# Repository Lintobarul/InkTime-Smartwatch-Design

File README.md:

# ⌚ InkTime - Open Source Smartwatch

**InkTime** este un smartwatch minimalist și eficient, proiectat pentru a fi open-source. Dispozitivul folosește un ecran E-Paper pentru un consum redus de energie și este motorizat de microcontrolerul nRF52840 (Cortex-M4F) cu suport Bluetooth 5.0.

## 1. Arhitectura Sistemului (Diagrama Bloc)
Dispozitivul este construit în jurul ecosistemului Nordic Semiconductor, integrând următoarele module principale:
* **Unitate Centrală:** nRF52840 (Sistem-on-Chip cu Bluetooth).
* **Afișaj:** E-Paper Display 1.54" (SPI).
* **Senzori:** BMA423 (Accelerometru/Pedometru) via I2C.
* **Management Energie:** BQ25180 (Charger) și MAX17048 (Fuel Gauge).
* **Haptics:** DRV2605 (Haptic Driver) pentru notificări prin vibrații.

---

## 2. Bill of Materials (BOM)

| RefDes | Componentă | Descriere | Link JLC Parts | Datasheet |
| :--- | :--- | :--- | :--- | :--- |
| U1 | nRF52840 | Microcontroller Bluetooth LE | [JLC Part](https://jlcpcb.com/parts/1/nRF52840) | [Datasheet](https://infocenter.nordicsemi.com/pdf/nRF52840_PS_v1.1.pdf) |
| U3 | MAX17048 | Fuel Gauge I2C | [JLC Part](https://jlcpcb.com/parts/1/MAX17048) | [Datasheet](https://datasheets.maximintegrated.com/en/ds/MAX17048-MAX17049.pdf) |
| J1 | 503480-2400 | Conector E-Paper 24-pin | [JLC Part](https://jlcpcb.com/parts/1/503480-2400) | [Datasheet](https://www.molex.com/pdm_docs/sd/5034802400_sd.pdf) |
| IC2 | DRV2605 | Haptic Driver (LRA/ERM) | [JLC Part](https://jlcpcb.com/parts/1/DRV2605) | [Datasheet](https://www.ti.com/lit/ds/symlink/drv2605.pdf) |
| J4 | USB-C 16P | Conector alimentare/date | [JLC Part](https://jlcpcb.com/parts/1/USB-C) | [Datasheet](...) |

---

## 3. Funcționalitate Hardware

### Managementul Energiei și Consum
Dispozitivul este alimentat de o baterie Li-Po de $150 \text{ mAh}$. Încărcarea este gestionată prin portul USB-C, iar nivelul bateriei este raportat prin I2C către procesor.
* **Calcul Autonomie:**
  Presupunând un consum mediu în regim de utilizare normală (Bluetooth activ, refresh ecran la 1 minut) de aproximativ $1.5 \text{ mA}$:
  $$\text{Autonomie} = \frac{150 \text{ mAh}}{1.5 \text{ mA}} = 100 \text{ ore} \approx 4.1 \text{ zile}$$

### Interfețe de Comunicare
* **SPI (Serial Peripheral Interface):** Folosit pentru ecranul E-Paper (semnale SCK, MOSI, CS) pentru a asigura o rată de transfer rapidă a buffer-ului de imagine.
* **I2C (Inter-Integrated Circuit):** Magistrală comună pentru BMA423, MAX17048 și DRV2605, optimizând numărul de pini utilizați.

---

## 4. Alocare Pini (Pinout nRF52840)

Am ales pinii procesorului pe baza funcțiilor speciale și a rutei optime pe PCB:

| Pin | Semnal | Funcție | Motiv |
| :--- | :--- | :--- | :--- |
| **P0.13** | SW_UP | Input | Butonul "SUS", necesită întrerupere pentru trezire. |
| **P0.14** | SW_ENT | Input | Butonul "ENTER", poziționat central. |
| **P1.02** | SW_DN | Input | Butonul "JOS". |
| **P1.13** | EPD_SCK | SPI Clock | Semnal ceas pentru display (Pagina 1.5B). |
| **P1.15** | EPD_MOSI | SPI Data | Date către display. |
| **P0.26** | I2C_SDA | Data | Linie de date pentru magistrala I2C. |
| **P0.27** | I2C_SCL | Clock | Linie de ceas pentru magistrala I2C. |

---

## 5. Design și Layout PCB
* **Grosime Placă:** $1.0 \text{ mm}$ (optimizat pentru carcasă).
* **Layer-ul TOP:** Toate componentele sunt montate pe acest strat pentru a facilita procesul de asamblare automată.
* **Antena RF:** Plasată pe marginea PCB-ului, cu planul de masă (GND) decupat dedesubt pentru a maximiza raza de acțiune Bluetooth.
* **Decuplare:** Condensatoarele de $100 \text{ nF}$ sunt plasate la o distanță de maxim $1 \text{ mm}$ de pinii VDD ai integratelor.

---

## 6. Imaginile Proiectului
### PCB Design (Top View)

### Ansamblu 3D (Exploded View)

---

## 7. Licență
Acest proiect este licențiat sub **GNU General Public License v3.0**. Consultați fișierul `LICENSE` pentru detalii.

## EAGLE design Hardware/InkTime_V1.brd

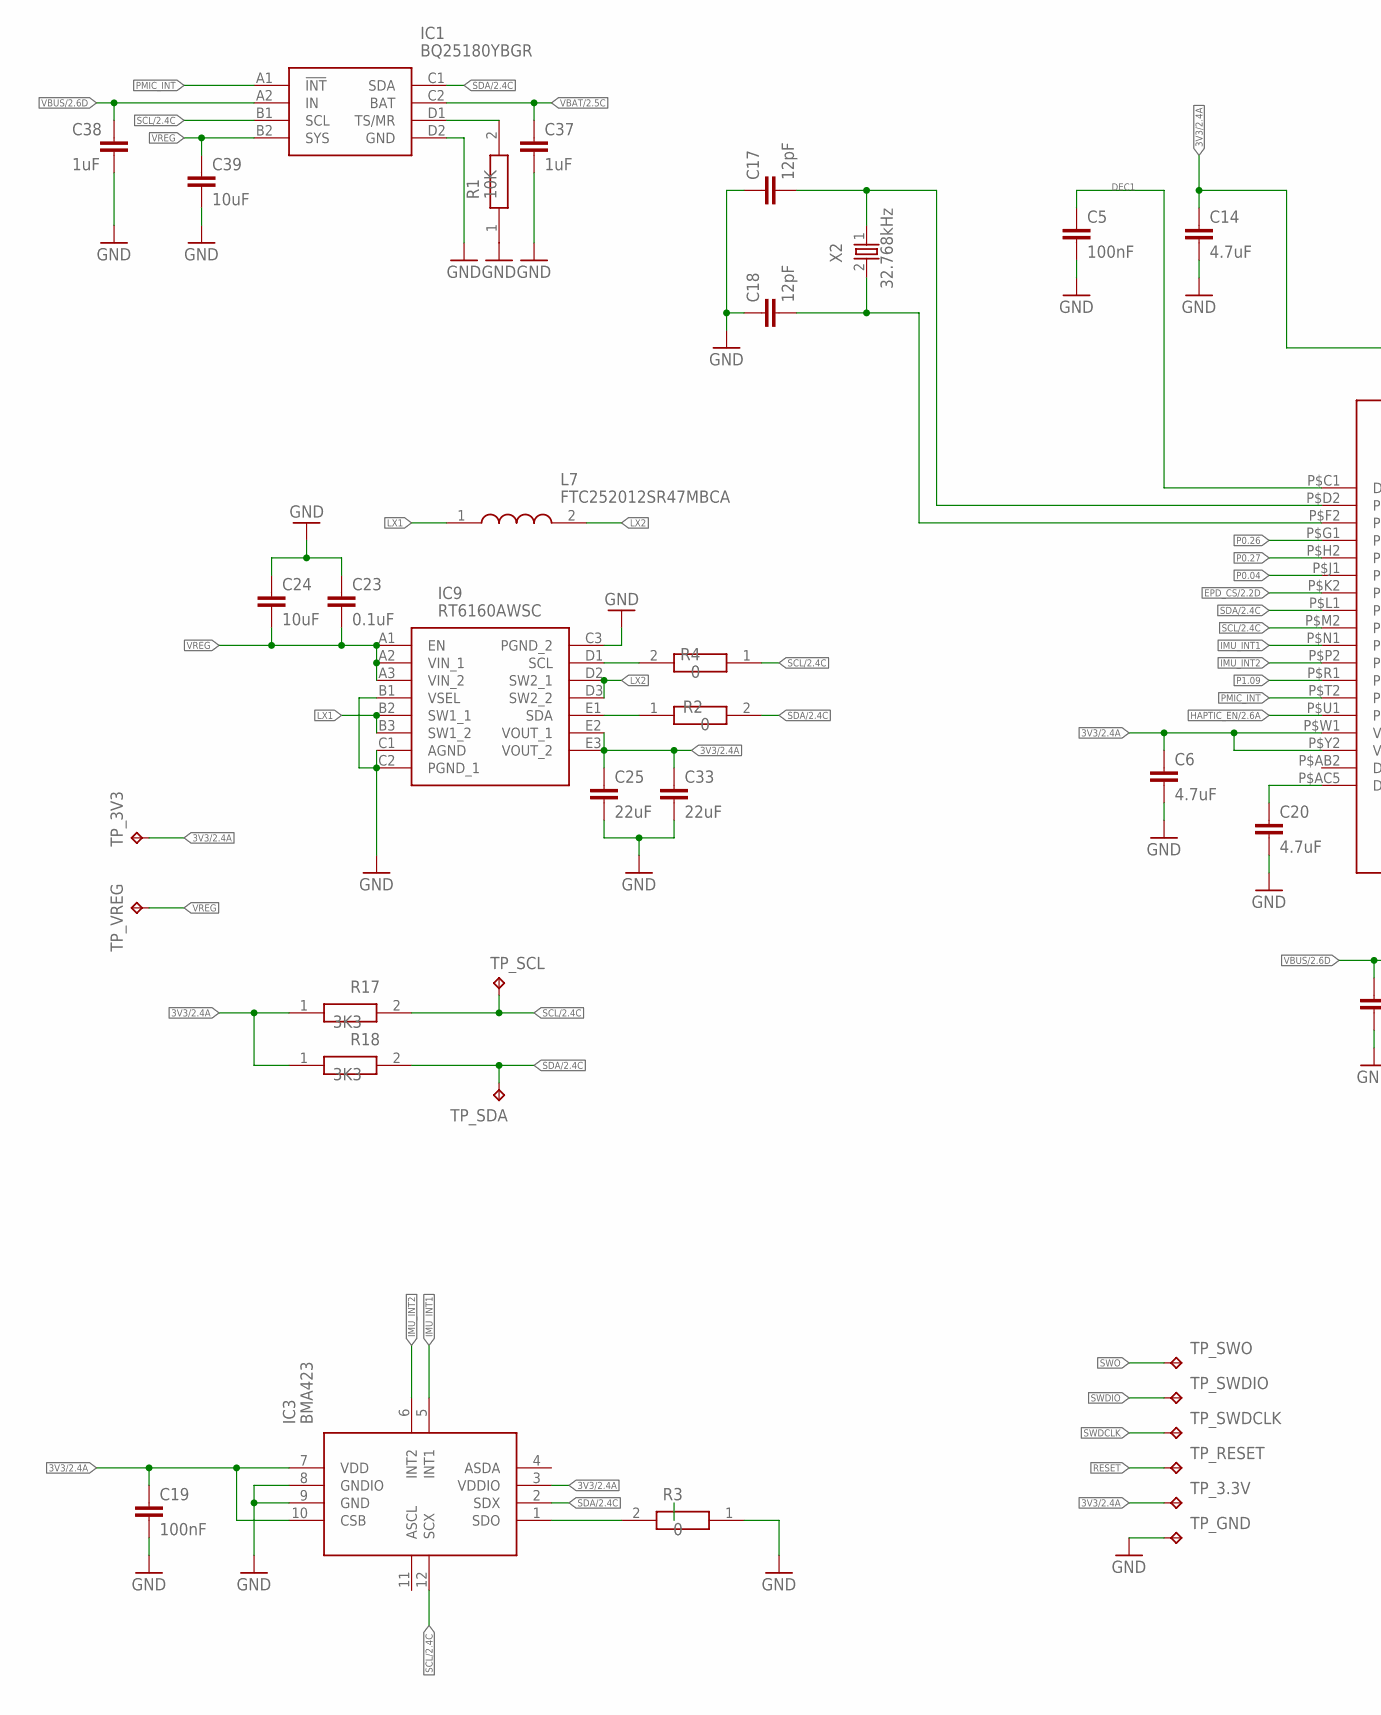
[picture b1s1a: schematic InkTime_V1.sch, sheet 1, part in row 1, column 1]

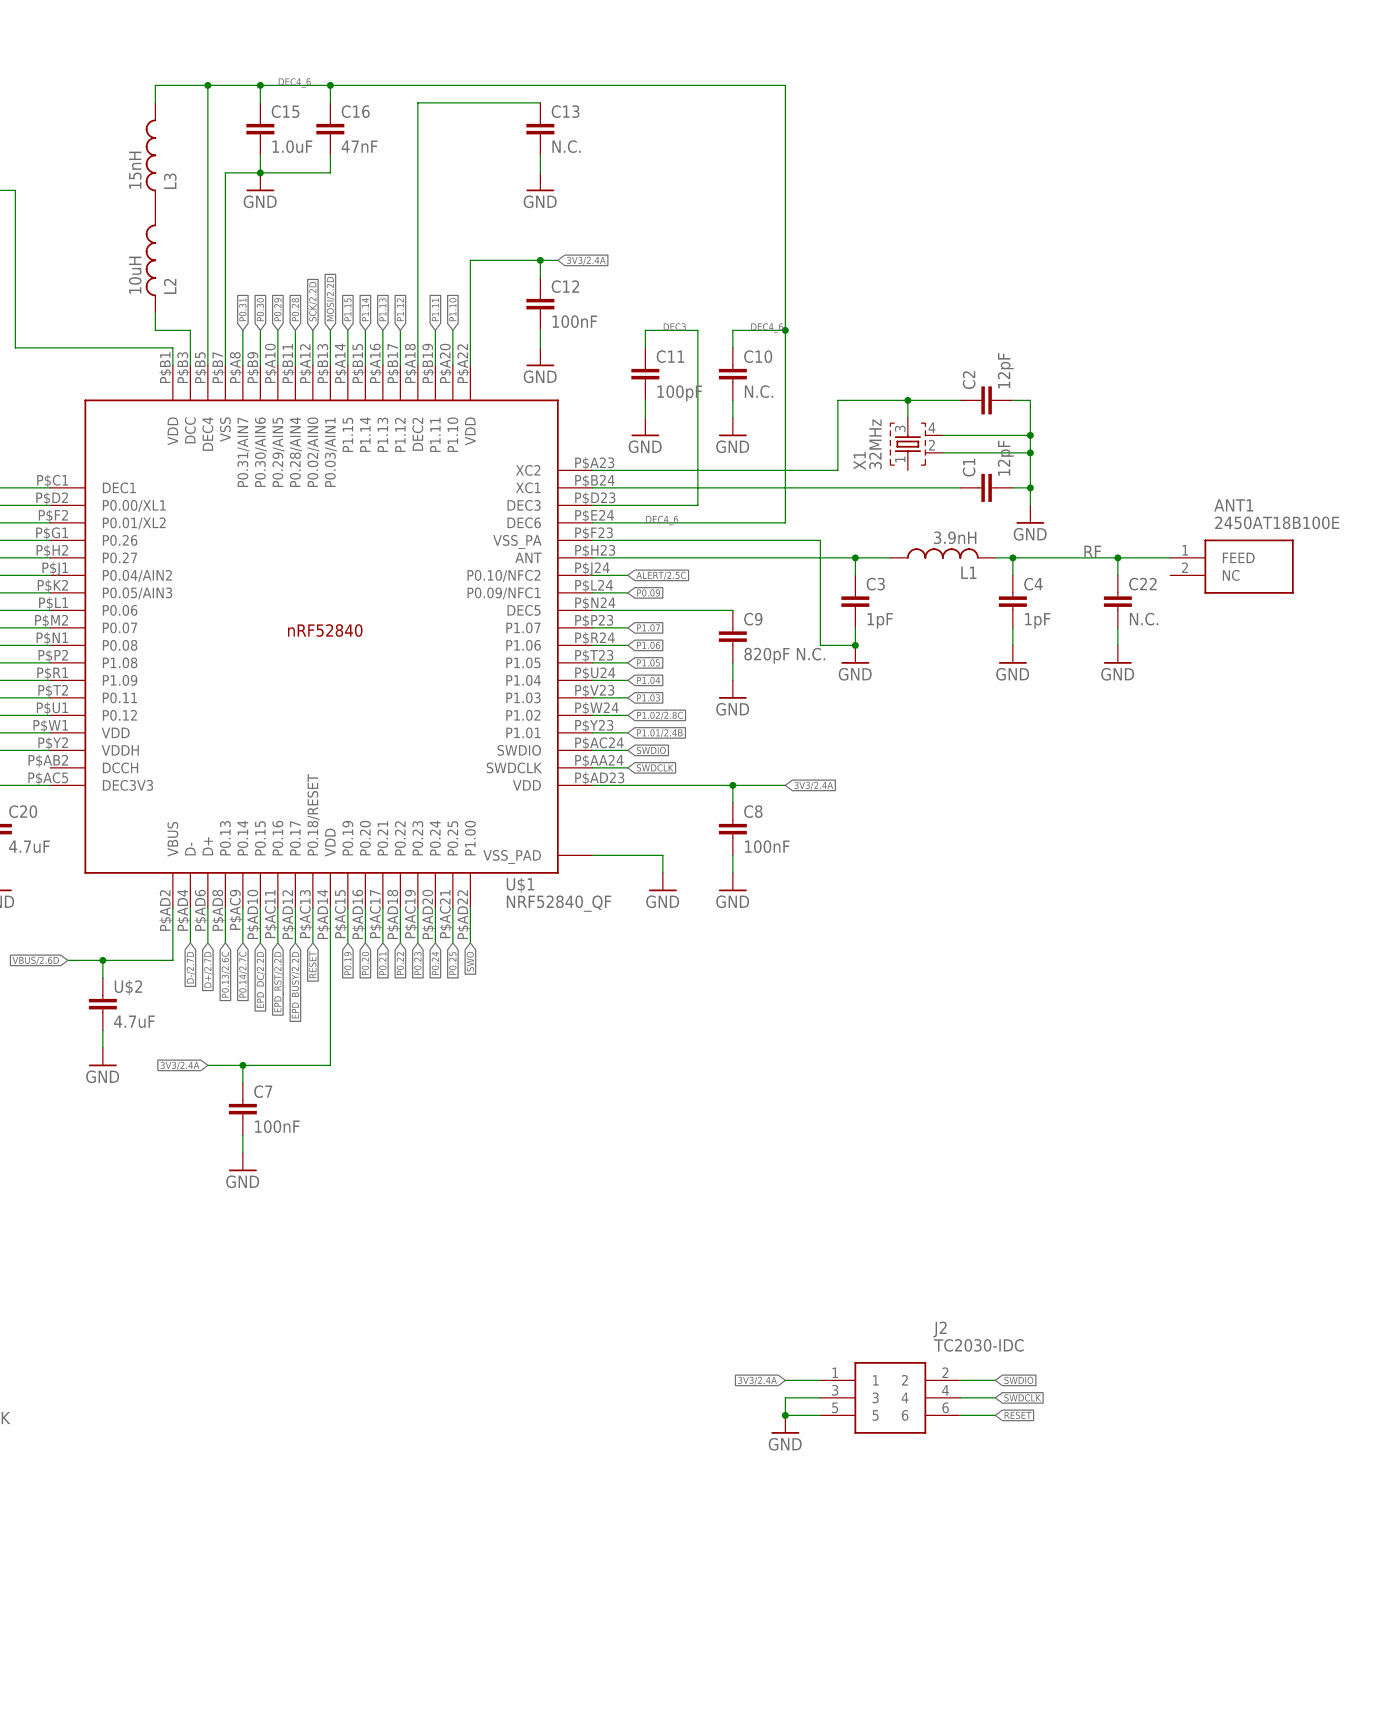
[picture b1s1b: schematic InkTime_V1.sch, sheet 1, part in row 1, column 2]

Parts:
ANT1: 2450AT18B100E; 2450AT18B100E_ANTC3216X140N
C1, C2, C17, C18: 12pF; NORDIC_NRF_3_RESC0201_L
C3, C4: 1pF; NORDIC_NRF_3_RESC0201_L
C5, C7, C8, C12, C19: 100nF; NORDIC_NRF_3_RESC0201_L
C6, C14, C20: 4.7uF; NORDIC_NRF_3_RESC0201_L
C9: 820pF N.C.; NORDIC_NRF_3_RESC0201_L
C10, C13, C22: N.C.; NORDIC_NRF_3_RESC0201_L
C11: 100pF; NORDIC_NRF_3_RESC0201_L
C15: 1.0uF; NORDIC_NRF_3_RESC0201_L
C16: 47nF; NORDIC_NRF_3_RESC0201_L
C23: 0.1uF; NORDIC_NRF_3_RESC0402_L
C24, C39: 10uF; NORDIC_NRF_3_RESC0201_L
C25, C33: 22uF; NORDIC_NRF_3_RESC0201_L
C37: 1uF; PERFECT_0402_0402
C38: 1uF; NORDIC_NRF_3_RESC0402_L
IC1: BQ25180YBGR; BQ25180YBGR_BGA8C40P2X4_100X155X50
IC3: BMA423; BMA423_BMA423
IC9: RT6160AWSC; RT6160AWSC_BGA15C40P3X5_140X230X60
J2: TC2030-IDC; TC2030-IDC_TC2030IDC
L1: 3.9nH; NORDIC_NRF_2_RESC0402_L
L2: 10uH; NORDIC_NRF_2_RESC0402_L
L3: 15nH; NORDIC_NRF_2_RESC0402_L
L7: FTC252012SR47MBCA; MLP2016SR47MT0S1_INDC2016X100N
R1: 10K; CPF0201D7K68C1_0201
R2, R3, R4: 0; CPF0201D7K68C1_0201
R17, R18: 3K3; CPF0201D7K68C1_0201
TP_3.3V, TP_3V3: HECTOR_WATCH_1_TPTP20R; HECTOR_WATCH_1_TP20R
TP_GND: HECTOR_WATCH_1_TPTP20R; HECTOR_WATCH_1_TP20R
TP_RESET: HECTOR_WATCH_1_TPTP20R; HECTOR_WATCH_1_TP20R
TP_SCL: HECTOR_WATCH_1_TPTP20R; HECTOR_WATCH_1_TP20R
TP_SDA: HECTOR_WATCH_1_TPTP20R; HECTOR_WATCH_1_TP20R
TP_SWDCLK: HECTOR_WATCH_1_TPTP20R; HECTOR_WATCH_1_TP20R
TP_SWDIO: HECTOR_WATCH_1_TPTP20R; HECTOR_WATCH_1_TP20R
TP_SWO: HECTOR_WATCH_1_TPTP20R; HECTOR_WATCH_1_TP20R
TP_VREG: HECTOR_WATCH_1_TPTP20R; HECTOR_WATCH_1_TP20R
U$1: NRF52840_QF; NORDIC_NRF_4_AQFN50P700X700X85_HS-74N
U$2: 4.7uF; NORDIC_NRF_3_RESC0201_L
X1: 32MHz; NORDIC_NRF_BT-XTAL_2016_N
X2: 32.768kHz; NORDIC_NRF_1_XTAL_3215_N

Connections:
3V3/2.4A: C6.1, C7.1, C8.1, C12.1, C14.1, C19.1, C25.1, C33.1, IC3.3 (VDDIO), IC3.7 (VDD), IC3.10 (CSB), IC9.E2 (VOUT_1), IC9.E3 (VOUT_2), J2.1, R17.1, R18.1, TP_3.3V.TP, TP_3V3.TP, U$1.P$A22 (VDD), U$1.P$AD14 (VDD), U$1.P$AD23 (VDD), U$1.P$B1 (VDD), U$1.P$W1 (VDD), U$1.P$Y2 (VDDH)
ALERT/2.5C: U$1.P$J24 (P0.10/NFC2)
D+/2.7D: U$1.P$AD6 (D+)
D-/2.7D: U$1.P$AD4 (D-)
DEC1: C5.1, U$1.P$C1 (DEC1)
DEC3: C11.1, U$1.P$D23 (DEC3)
DEC4_6: C10.1, C15.1, C16.1, L3.1, U$1.P$B5 (DEC4), U$1.P$E24 (DEC6)
EPD_BUSY/2.2D: U$1.P$AD12 (P0.17)
EPD_CS/2.2D: U$1.P$K2 (P0.05/AIN3)
EPD_DC/2.2D: U$1.P$AD10 (P0.15)
EPD_RST/2.2D: U$1.P$AC11 (P0.16)
GND: C1.2, C2.2, C3.2, C4.2, C5.2, C6.2, C7.2, C8.2, C9.2, C10.2, C11.2, C12.2, C13.2, C14.2, C15.2, C16.2, C17.1, C18.1, C19.2, C20.2, C22.2, C23.1, C24.1, C25.2, C33.2, C37.2, C38.2, C39.2, IC1.D2 (GND), IC3.8 (GNDIO), IC3.9 (GND), IC9.B1 (VSEL), IC9.C1 (AGND), IC9.C2 (PGND_1), IC9.C3 (PGND_2), J2.3, J2.5, R1.1, R3.1, TP_GND.TP, U$1.P$74 (VSS_PAD), U$1.P$75 (VSS_PAD), U$1.P$76 (VSS_PAD), U$1.P$77 (VSS_PAD), U$1.P$78 (VSS_PAD), U$1.P$79 (VSS_PAD), U$1.P$80 (VSS_PAD), U$1.P$81 (VSS_PAD), U$1.P$82 (VSS_PAD), U$1.P$83 (VSS_PAD), U$1.P$84 (VSS_PAD), U$1.P$85 (VSS_PAD), U$1.P$86 (VSS_PAD), U$1.P$87 (VSS_PAD), U$1.P$88 (VSS_PAD), U$1.P$89 (VSS_PAD), U$1.P$90 (VSS_PAD), U$1.P$B7 (VSS), U$1.P$F23 (VSS_PA), U$2.2, X1.2, X1.4; also elsewhere on the board
HAPTIC_EN/2.6A: U$1.P$U1 (P0.12)
IMU_INT1: IC3.5 (INT1), U$1.P$N1 (P0.08)
IMU_INT2: IC3.6 (INT2), U$1.P$P2 (P1.08)
LX1: IC9.B2 (SW1_1), IC9.B3 (SW1_2), L7.1
LX2: IC9.D2 (SW2_1), IC9.D3 (SW2_2), L7.2
MOSI/2.2D: U$1.P$B13 (P0.03/AIN1)
unnamed: C1.1, U$1.P$B24 (XC1)
unnamed: C2.1, U$1.P$A23 (XC2), X1.3
unnamed: L2.1, L3.2
unnamed: L2.2, U$1.P$B3 (DCC)
unnamed: C3.1, L1.1, U$1.P$H23 (ANT)
unnamed: C9.1, U$1.P$N24 (DEC5)
unnamed: C17.2, U$1.P$D2 (P0.00/XL1), X2.1
unnamed: C20.1, U$1.P$AC5 (DEC3V3)
unnamed: C18.2, U$1.P$F2 (P0.01/XL2), X2.2
unnamed: IC3.1 (SDO), R3.2
unnamed: IC1.D1 (TS/MR), R1.2
unnamed: IC9.D1 (SCL), R4.2
unnamed: IC9.E1 (SDA), R2.1
unnamed: C13.1, U$1.P$A18 (DEC2)
P0.04: U$1.P$J1 (P0.04/AIN2)
P0.09: U$1.P$L24 (P0.09/NFC1)
P0.13/2.6C: U$1.P$AD8 (P0.13)
P0.14/2.7C: U$1.P$AC9 (P0.14)
P0.19: U$1.P$AC15 (P0.19)
P0.20: U$1.P$AD16 (P0.20)
P0.21: U$1.P$AC17 (P0.21)
P0.22: U$1.P$AD18 (P0.22)
P0.23: U$1.P$AC19 (P0.23)
P0.24: U$1.P$AD20 (P0.24)
P0.25: U$1.P$AC21 (P0.25)
P0.26: U$1.P$G1 (P0.26)
P0.27: U$1.P$H2 (P0.27)
P0.28: U$1.P$B11 (P0.28/AIN4)
P0.29: U$1.P$A10 (P0.29/AIN5)
P0.30: U$1.P$B9 (P0.30/AIN6)
P0.31: U$1.P$A8 (P0.31/AIN7)
P1.01/2.4B: U$1.P$Y23 (P1.01)
P1.02/2.8C: U$1.P$W24 (P1.02)
P1.03: U$1.P$V23 (P1.03)
P1.04: U$1.P$U24 (P1.04)
P1.05: U$1.P$T23 (P1.05)
P1.06: U$1.P$R24 (P1.06)
P1.07: U$1.P$P23 (P1.07)
P1.09: U$1.P$R1 (P1.09)
P1.10: U$1.P$A20 (P1.10)
P1.11: U$1.P$B19 (P1.11)
P1.12: U$1.P$B17 (P1.12)
P1.13: U$1.P$A16 (P1.13)
P1.14: U$1.P$B15 (P1.14)
P1.15: U$1.P$A14 (P1.15)
PMIC_INT: IC1.A1 (!INT), U$1.P$T2 (P0.11)
RESET: J2.6, TP_RESET.TP, U$1.P$AC13 (P0.18/RESET)
RF: ANT1.1 (FEED), C4.1, C22.1, L1.2
SCK/2.2D: U$1.P$A12 (P0.02/AIN0)
SCL/2.4C: IC1.B1 (SCL), IC3.12 (SCX), R4.1, R17.2, TP_SCL.TP, U$1.P$M2 (P0.07)
SDA/2.4C: IC1.C1 (SDA), IC3.2 (SDX), R2.2, R18.2, TP_SDA.TP, U$1.P$L1 (P0.06)
SWDCLK: J2.4, TP_SWDCLK.TP, U$1.P$AA24 (SWDCLK)
SWDIO: J2.2, TP_SWDIO.TP, U$1.P$AC24 (SWDIO)
SWO: TP_SWO.TP, U$1.P$AD22 (P1.00)
VBAT/2.5C: C37.1, IC1.C2 (BAT)
VBUS/2.6D: C38.1, IC1.A2 (IN), U$1.P$AD2 (VBUS), U$2.1
VREG: C23.2, C24.2, C39.1, IC1.B2 (SYS), IC9.A1 (EN), IC9.A2 (VIN_1), IC9.A3 (VIN_2), TP_VREG.TP

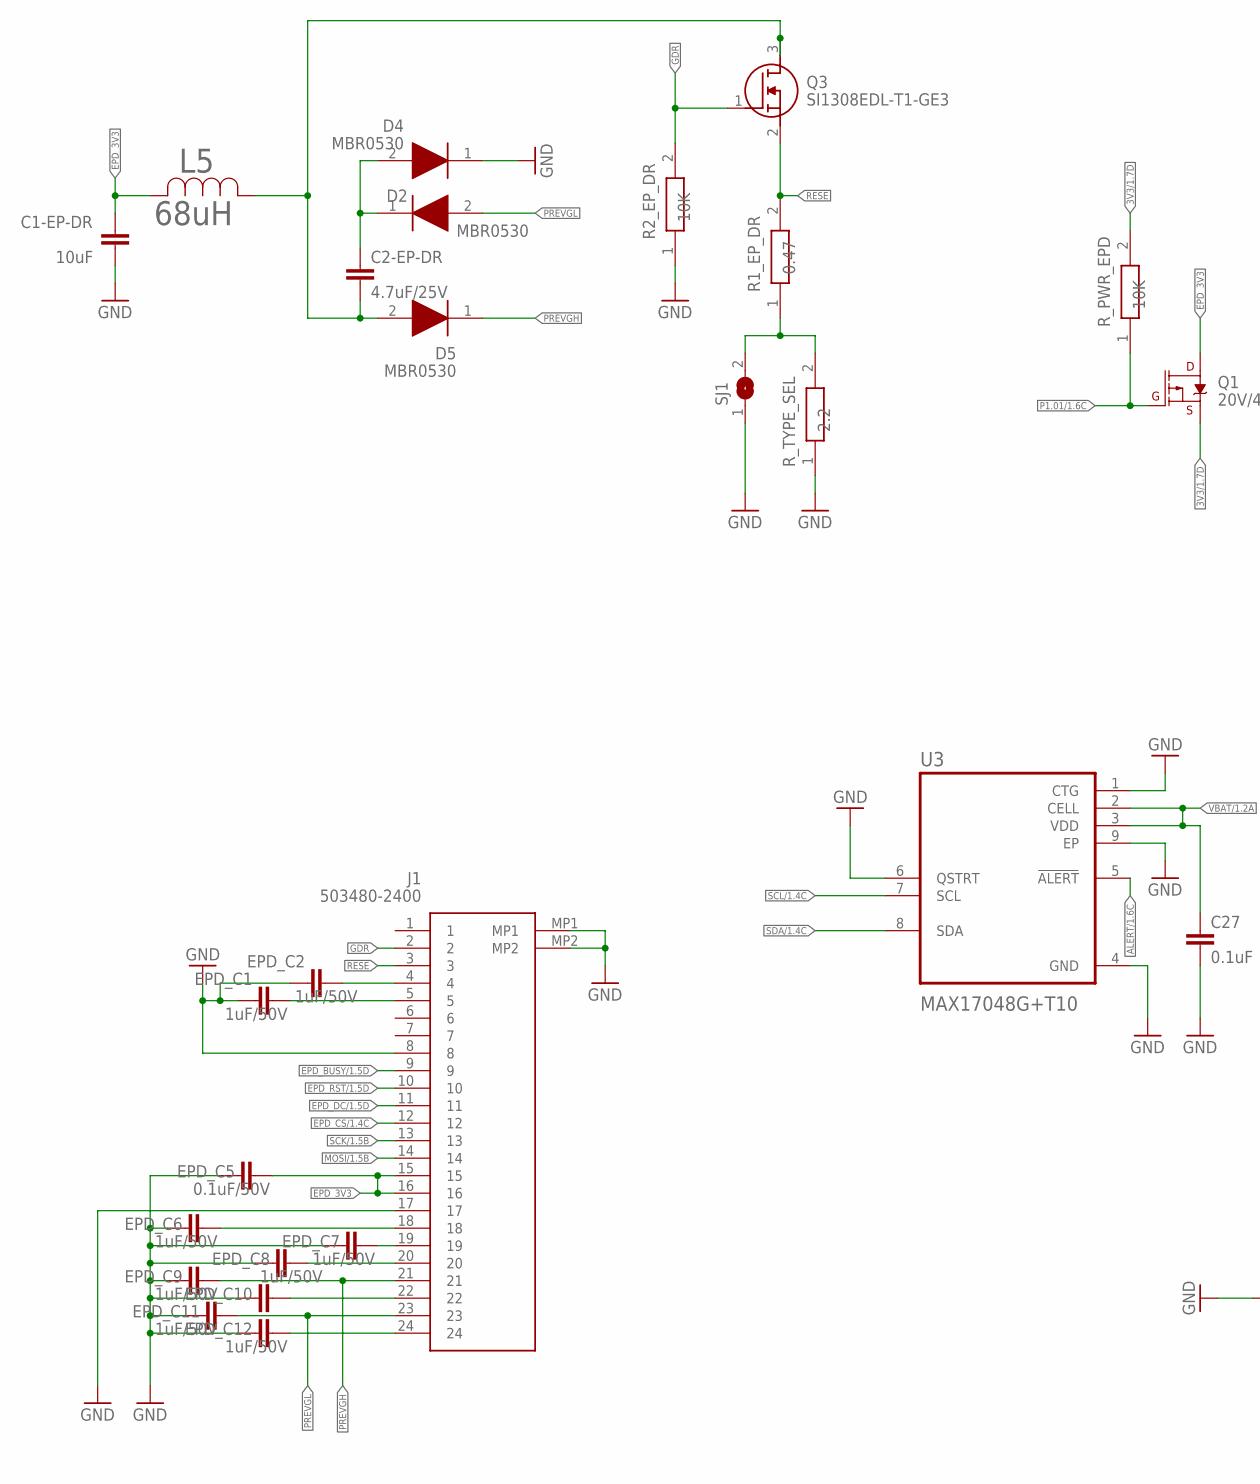
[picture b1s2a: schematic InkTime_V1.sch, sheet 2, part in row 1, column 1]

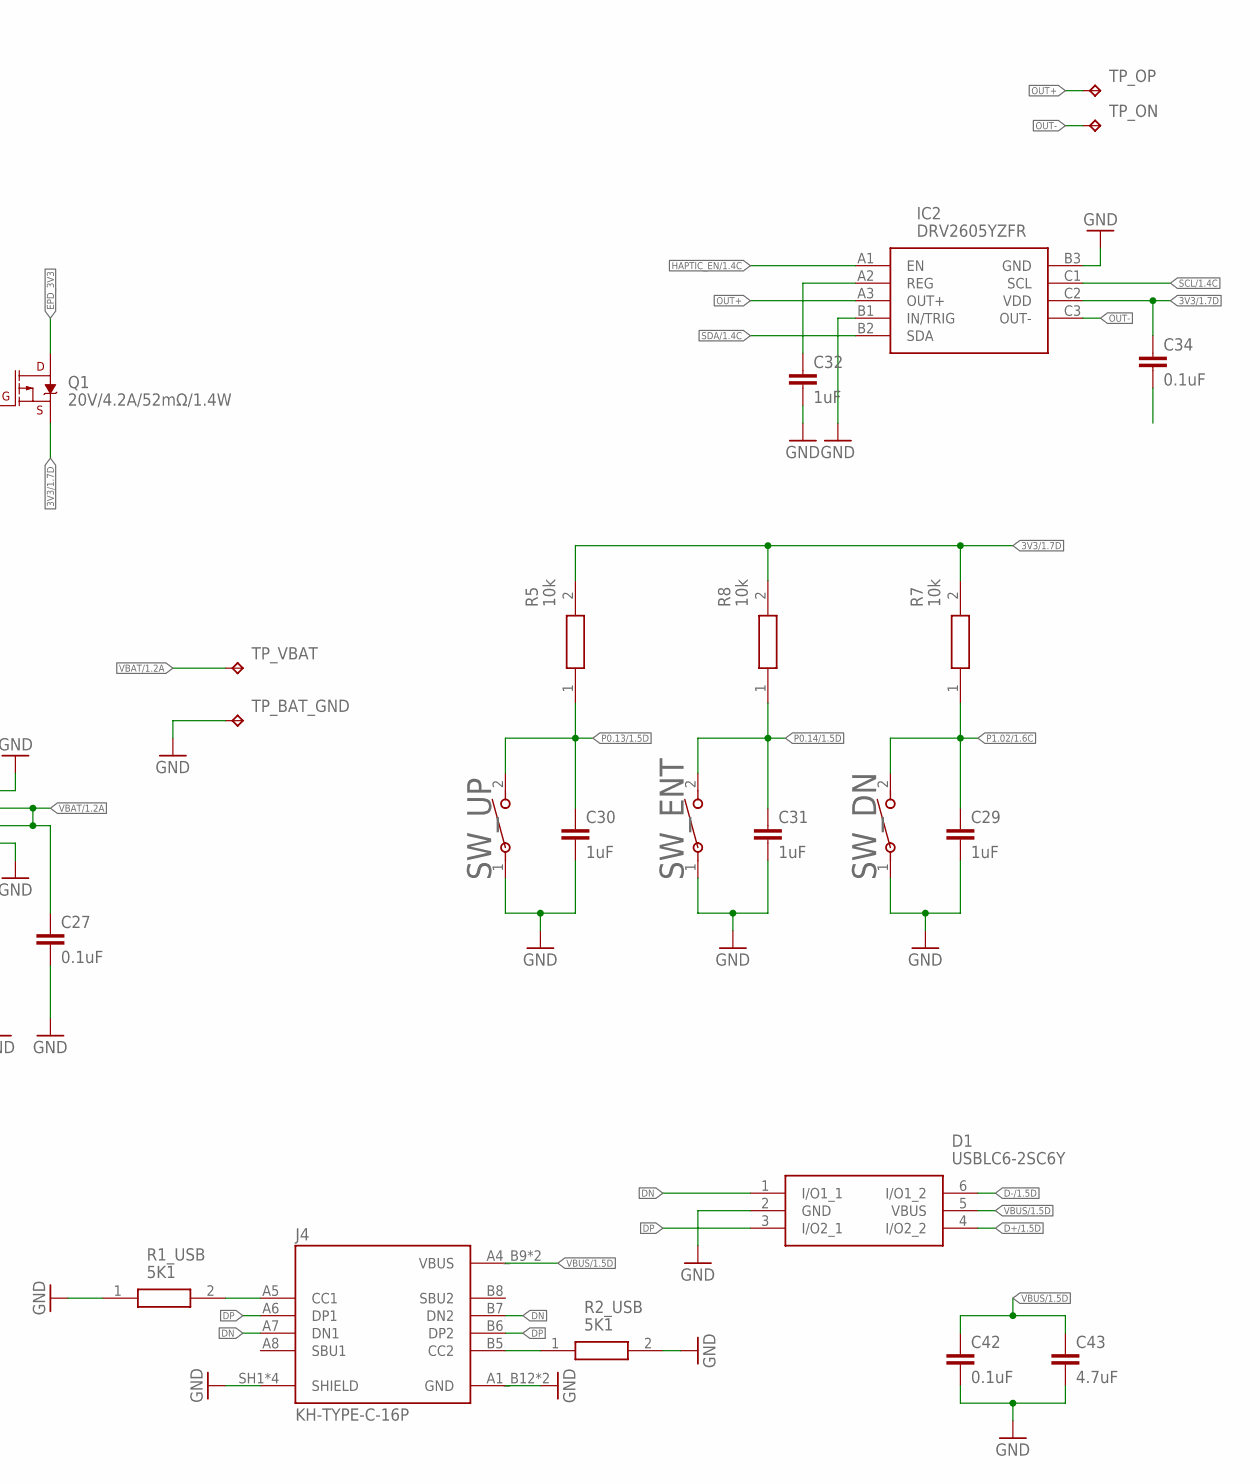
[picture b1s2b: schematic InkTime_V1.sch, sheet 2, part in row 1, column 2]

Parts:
C1-EP-DR: 10uF; NORDIC_NRF_3_RESC0201_L
C2-EP-DR: 4.7uF/25V; NORDIC_NRF_3_RESC0201_L
C27, C34, C42: 0.1uF; NORDIC_NRF_3_RESC0402_L
C29, C30, C31, C32: 1uF; NORDIC_NRF_3_RESC0402_L
C43: 4.7uF; NORDIC_NRF_3_RESC0201_L
D1: USBLC6-2SC6Y; ESP32_C6_LIBRARY_3_SOT95P280X145-6N
D2, D4, D5: MBR0530; ESP32_C6_LIBRARY_5_SOD3716X135N
EPD_C1, EPD_C2, EPD_C6, EPD_C7, EPD_C8, EPD_C9, EPD_C11, EPD_C12: 1uF/50V; NORDIC_NRF_3_RESC0201_L
EPD_C5: 0.1uF/50V; NORDIC_NRF_3_RESC0201_L
EPD_C10: NORDIC_NRF_3_CAPACITOR_0201_L; NORDIC_NRF_3_RESC0201_L
IC2: DRV2605YZFR; DRV2605YZFR_BGA9C50P3X3_144X144X62
J1: 503480-2400; 503480-2400_5034802400
J4: KH-TYPE-C-16P; KH-TYPE-C-16P_KINGHELM_KH-TYPE-C-16P
L5: 68uH; ESP32_C6_LIBRARY_2_IND_4828-WE-TPC_WRE
Q1: 20V/4.2A/52mΩ/1.4W; ESP32_C6_LIBRARY_4_ESP32_C6_LIBRARY_4_ESP32_C6_LIBRARY_4_ES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
Q3: SI1308EDL-T1-GE3; ESP32_C6_LIBRARY_6_SOT65P210X110-3N
R1_EP_DR: 0.47; CPF0201D7K68C1_0201
R1_USB, R2_USB: 5K1; CPF0201D7K68C1_0201
R2_EP_DR: 10K; ERA-1AEB3401C_0201
R5, R7, R8: 10k; CPF0201D7K68C1_0201
R_PWR_EPD: 10K; CPF0201D7K68C1_0201
R_TYPE_SEL: 2.2; CPF0201D7K68C1_0201
SJ1: ESP32_C6_LIBRARY_7_JUMPER_SJ
SW_DN: 2025-10-22_07-23-44_LIBRARY_EVP-AKE31ASW_EVP-AKE3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; 2025-10-22_07-23-44_LIBRARY_SW_EVP-AKE31A_PAN
SW_ENT: 2025-10-22_07-23-44_LIBRARY_EVP-AKE31ASW_EVP-AKE3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; 2025-10-22_07-23-44_LIBRARY_SW_EVP-AKE31A_PAN
SW_UP: 2025-10-22_07-23-44_LIBRARY_EVP-AKE31ASW_EVP-AKE3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; 2025-10-22_07-23-44_LIBRARY_SW_EVP-AKE31A_PAN
TP_BAT_GND: HECTOR_WATCH_1_TPTP20R; HECTOR_WATCH_1_TP20R
TP_ON: HECTOR_WATCH_1_TPTP20R; HECTOR_WATCH_1_TP20R
TP_OP: HECTOR_WATCH_1_TPTP20R; HECTOR_WATCH_1_TP20R
TP_VBAT: HECTOR_WATCH_1_TPTP20R; HECTOR_WATCH_1_TP20R
U3: MAX17048G+T10; ESP32_C6_LIBRARY_SON50P200X200X80-9N

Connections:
3V3/1.7D: C34.1, IC2.C2 (VDD), Q1.2 (S), R5.2, R7.2, R8.2, R_PWR_EPD.2
ALERT/1.6C: U3.5 (!ALERT)
D+/1.5D: D1.4 (I/O2_2)
D-/1.5D: D1.6 (I/O1_2)
DN: D1.1 (I/O1_1), J4.A7 (DN1), J4.B7 (DN2)
DP: D1.3 (I/O2_1), J4.A6 (DP1), J4.B6 (DP2)
EPD_3V3: C1-EP-DR.1, EPD_C5.2, J1.15, J1.16, L5.2, Q1.3 (D)
EPD_BUSY/1.5D: J1.9
EPD_CS/1.4C: J1.12
EPD_DC/1.5D: J1.11
EPD_RST/1.5D: J1.10
GDR: J1.2, Q3.1 (G), R2_EP_DR.2
GND: C1-EP-DR.2, C27.2, C29.2, C30.2, C31.2, C32.2, C42.2, C43.2, D1.2 (GND), D4.1 (K), EPD_C1.1, EPD_C2.1, EPD_C5.1, EPD_C6.1, EPD_C7.1, EPD_C8.1, EPD_C9.1, EPD_C10.1, EPD_C11.1, EPD_C12.1, IC2.B1 (IN/TRIG), IC2.B3 (GND), J1.8, J1.17, J1.MP1, J1.MP2, J4.A1_B12 (GND), J4.A12_B1 (GND), J4.SH1 (SHIELD), J4.SH2 (SHIELD), J4.SH3 (SHIELD), J4.SH4 (SHIELD), R1_USB.1, R2_EP_DR.1, R2_USB.2, R_TYPE_SEL.1, SJ1.1, SW_DN.1, SW_ENT.1, SW_UP.1, TP_BAT_GND.TP, U3.1 (CTG), U3.4 (GND), U3.6 (QSTRT), U3.9 (EP); also elsewhere on the board
HAPTIC_EN/1.4C: IC2.A1 (EN)
MOSI/1.5B: J1.14
unnamed: C2-EP-DR.2, D5.2 (A), L5.1, Q3.3 (D)
unnamed: C2-EP-DR.1, D2.1 (K), D4.2 (A)
unnamed: R1_EP_DR.1, R_TYPE_SEL.2, SJ1.2
unnamed: EPD_C1.2, J1.5
unnamed: EPD_C2.2, J1.4
unnamed: J4.B5 (CC2), R2_USB.1
unnamed: J4.A5 (CC1), R1_USB.2
unnamed: EPD_C12.2, J1.24
unnamed: C32.1, IC2.A2 (REG)
unnamed: EPD_C8.2, J1.20
unnamed: EPD_C7.2, J1.19
unnamed: EPD_C6.2, J1.18
unnamed: EPD_C10.2, J1.22
OUT+: IC2.A3 (OUT+), TP_OP.TP
OUT-: IC2.C3 (OUT-), TP_ON.TP
P0.13/1.5D: C30.1, R5.1, SW_UP.2
P0.14/1.5D: C31.1, R8.1, SW_ENT.2
P1.01/1.6C: Q1.1 (G), R_PWR_EPD.1
P1.02/1.6C: C29.1, R7.1, SW_DN.2
PREVGH: D5.1 (K), EPD_C9.2, J1.21
PREVGL: D2.2 (A), EPD_C11.2, J1.23
RESE: J1.3, Q3.2 (S), R1_EP_DR.2
SCK/1.5B: J1.13
SCL/1.4C: IC2.C1 (SCL), U3.7 (SCL)
SDA/1.4C: IC2.B2 (SDA), U3.8 (SDA)
VBAT/1.2A: C27.1, TP_VBAT.TP, U3.2 (CELL), U3.3 (VDD)
VBUS/1.5D: C42.1, C43.1, D1.5 (VBUS), J4.A4_B9 (VBUS), J4.A9_B4 (VBUS)

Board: 2 copper layers, 105 parts (0 on the bottom side), 65 nets, no tracks yet.

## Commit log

2026-04-15 Create 3d
2026-04-15 Create pcb
2026-04-15 Create schema_electrica
2026-04-15 Rename InkTime_V1.csv to gerbers.csv

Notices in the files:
parts and their libraries:
COPYRIGHT: Copyright (C) 2024 Ultra Librarian. All rights reserved.
COPYRIGHT: Copyright (C) 2025 Ultra Librarian. All rights reserved.
